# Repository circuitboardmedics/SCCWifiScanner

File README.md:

# SCC Wifi Scanner

</p>

# Overview
SCC Wifi Scanner is a custom electronics project for Spartanburg Community College's Computer Club, forked from the 2023 soldering village at [BSides 2023 Cybersecurity conference in Greenville, SC. ](https://github.com/circuitboardmedics/BSidesWifiScanner) 

This device is capable of scanning Wi-Fi networks, displaying the AP's MAC, the network's encryption type, as well as the current channel and RSSI.  It can also graphically display the signal strength of individual networks. The firmware features modular button handling, a timer for display fields, and a page manager for different UI screens.

# Assembly
A soldering iron and basic soldering skills are required to assemble the kit, but no other special tools are needed.  

## Diagram
Follow the diagram below for component placement. 

## Tips
1. Suggested soldering order: `U2`, `U1`, `Buttons`, `C1`, `SW0`, `BT1`

1. Polarity (Orientation) of `BT1`, `C1`, and `U2` matters; follow the diagram for placement.  The Capacitor C1 has white stripe on one side that should align with the white marking on the board.

1. Install the battery into the clip LAST, so as to avoid any short circuits during assembly.
   
1. Clip the long legs off the capacitor once soldered so they do not short to each other or anything else.

1. Residue left from soldering can be cleaned with Isopropyl alcohol.

1. The optional female headers can be used instead of mounting `U2` directly to the board, in order to make it removable.  Alternatively, they can be mounted adjacent to `U2` to provide access to the GPIO pins of the microcontroller.

## Video

_(note that the capacitor is shown installed backwards in the video. the white stripe should align with the white marking on the pcb)_

## Component Bill Of Materials:
- [1.3 Inch IIC I2C OLED Display Module 128x64 Pixel SH1106 Screen Module](https://www.amazon.com/gp/product/B0C3L7N917/) (U1)
- [WeMos D1 Mini microcontroller](https://www.amazon.com/s?k=wemos+d1+mini) (U2)
- [SPST Micro Switch](https://www.amazon.com/gp/product/B07BD1SPYG) (SW0)
- 1 [Tactile momentary switch 6x6x5 mm](https://www.amazon.com/gp/product/B01CGMP9G) (Left, Center, Right)
- ~100uF Electrolytic capacitor (C1)
- CR123 Battery (BT1)

## PCB
KiCad design files for the PCB, including schematic, are included in the pcb folder.

# Programming 
The microcontrollers are pre-flashed with the WiFi scanner firmware, but can be re-programmed with any other custom firmware following the tutorial below.

## Prerequisites
- USB Micro cable
- Visual Studio Code
- PlatformIO IDE extension
- ESP8266 or compatible board

## Setup Environment Using Visual Studio Code and PlatformIO

1. **Install Visual Studio Code**: Download and install [Visual Studio Code](https://code.visualstudio.com/).

2. **Install PlatformIO**: Open Visual Studio Code, go to Extensions and search for "PlatformIO IDE". Install it.

3. **Clone the Repository**: Clone this repository to your local machine using Git.

4. **Open the Project**: Open Visual Studio Code and navigate to `File > Open Folder` and select the cloned repository folder.

5. **PlatformIO Initialization**: The repository contains a [`platformio.ini`](https://github.com/circuitboardmedics/BSidesWifiScanner/blob/main/platformio.ini) file that specifies the board and dependencies. PlatformIO should automatically recognize this.

6. **Install Dependencies**: PlatformIO will automatically install the required libraries specified in `platformio.ini`.

## Flashing the Code

1. **Select Environment**: In PlatformIO Home, select the environment that matches your board. The default in `platformio.ini` is `d1_mini`.

2. **Build the Project**: Click on the "Build" button (checkmark icon) in the PlatformIO toolbar at the bottom.

3. **Upload the Code**: After a successful build, click on the "Upload" button (right arrow icon) in the PlatformIO toolbar to flash the code to your board.

4. **Monitor Serial Output**: Optionally, you can open the Serial Monitor by clicking on the "Serial Monitor" button (plug icon) in the PlatformIO toolbar to view debug output.

# Usage
After flashing, the device will start scanning for Wi-Fi networks and display a graphical representation of the signal strength for individual networks. Use the buttons to navigate through different pages.

# Thank you

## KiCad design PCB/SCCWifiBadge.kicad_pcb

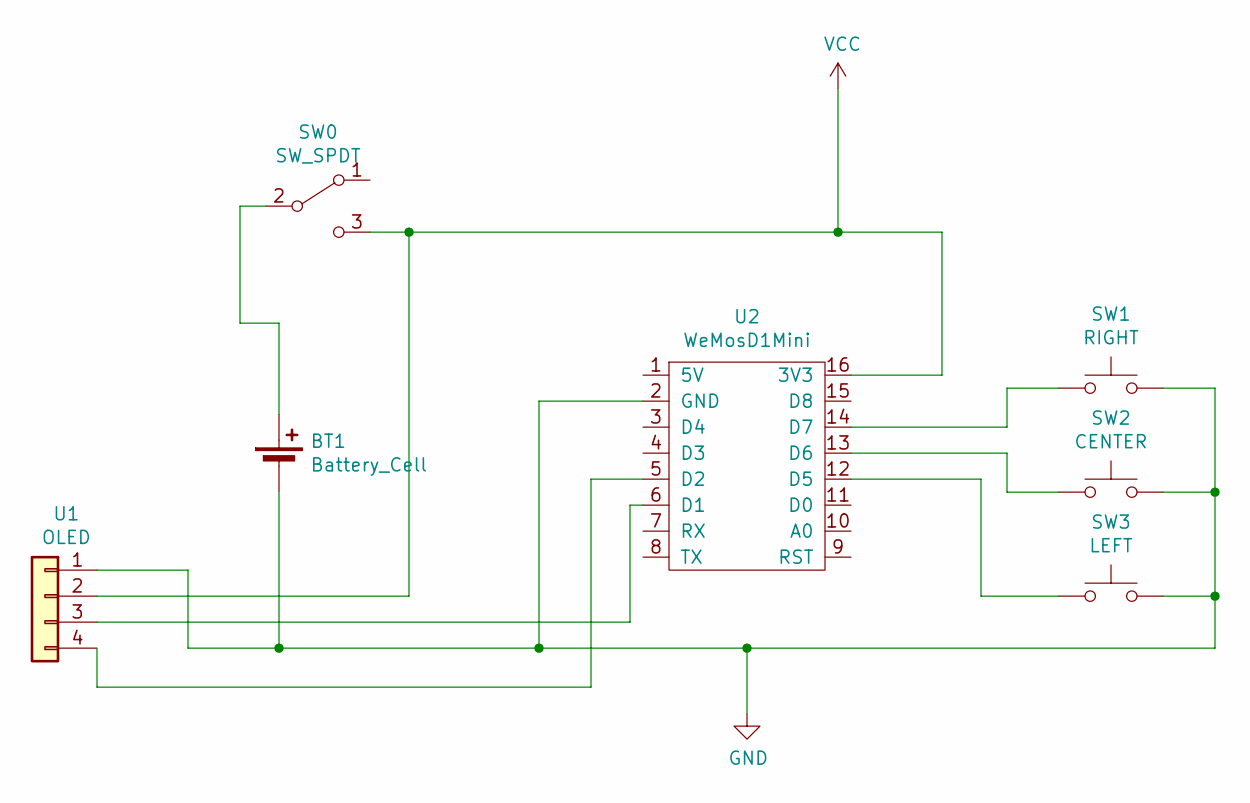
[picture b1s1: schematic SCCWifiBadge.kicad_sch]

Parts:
BT1: Battery_Cell; CR123A
SW0: SW_SPDT; PinHeader_1x03_P2.54mm_Vertical
SW1: RIGHT; SW_Tactile_Straight_KSA0Axx1LFTR
SW2: CENTER; SW_Tactile_Straight_KSA0Axx1LFTR
SW3: LEFT; SW_Tactile_Straight_KSA0Axx1LFTR
U1: OLED; PinHeader_1x04_P2.54mm_Vertical
U2: WeMosD1Mini

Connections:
GND: BT1.2 (-), SW1.2, SW2.2, SW3.2, U1.1, U2.2 (GND); also elsewhere on the board
unnamed: BT1.1 (+), SW0.2 (B)
unnamed: SW1.1, U2.14 (D7)
unnamed: SW2.1, U2.13 (D6)
unnamed: SW3.1, U2.12 (D5)
unnamed: U1.3, U2.6 (D1)
unnamed: U1.4, U2.5 (D2)
VCC: SW0.3 (C), U1.2, U2.16 (3V3); also elsewhere on the board

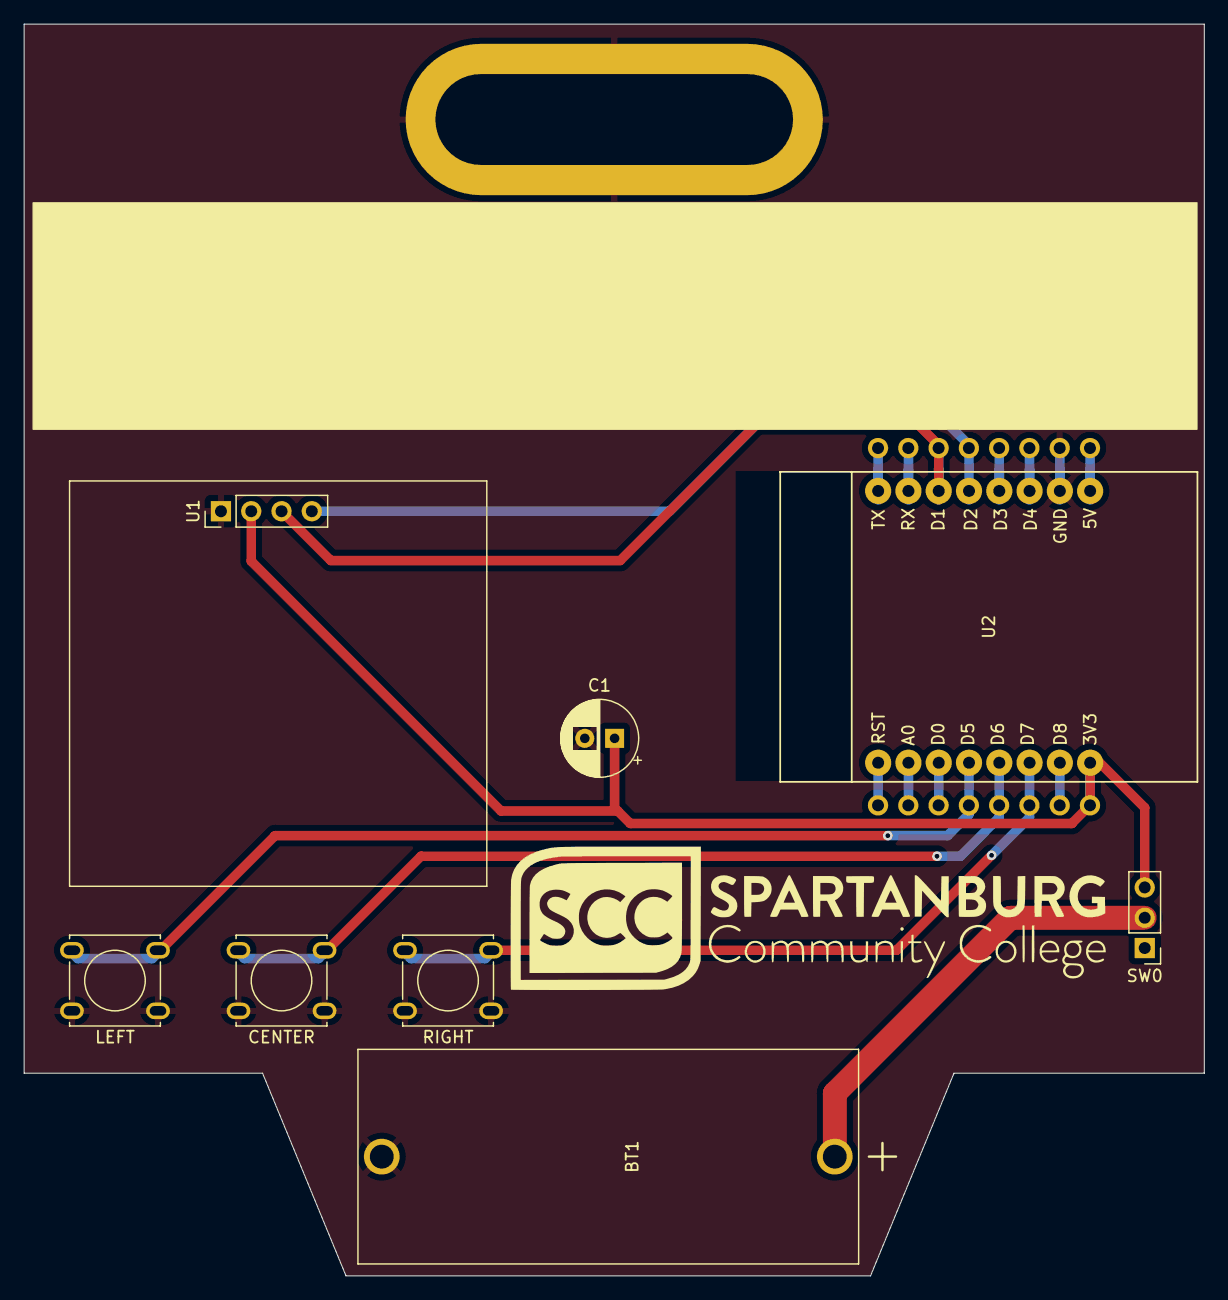
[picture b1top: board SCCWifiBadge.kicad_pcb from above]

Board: 2 copper layers, 99.0 x 105.0 mm, 8 parts (0 on the bottom side), 8 nets.

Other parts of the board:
C1: CP_Radial_D6.3mm_P2.50mm

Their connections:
GND: C1.2; also elsewhere on the board
VCC: C1.1; also elsewhere on the board

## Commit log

2023-11-17 update splash screen logo for SCC
2023-11-20 add kicad pcb files
2023-11-21 update readme for SCC, add image resources
2023-11-22 fix cloning issue on windows
